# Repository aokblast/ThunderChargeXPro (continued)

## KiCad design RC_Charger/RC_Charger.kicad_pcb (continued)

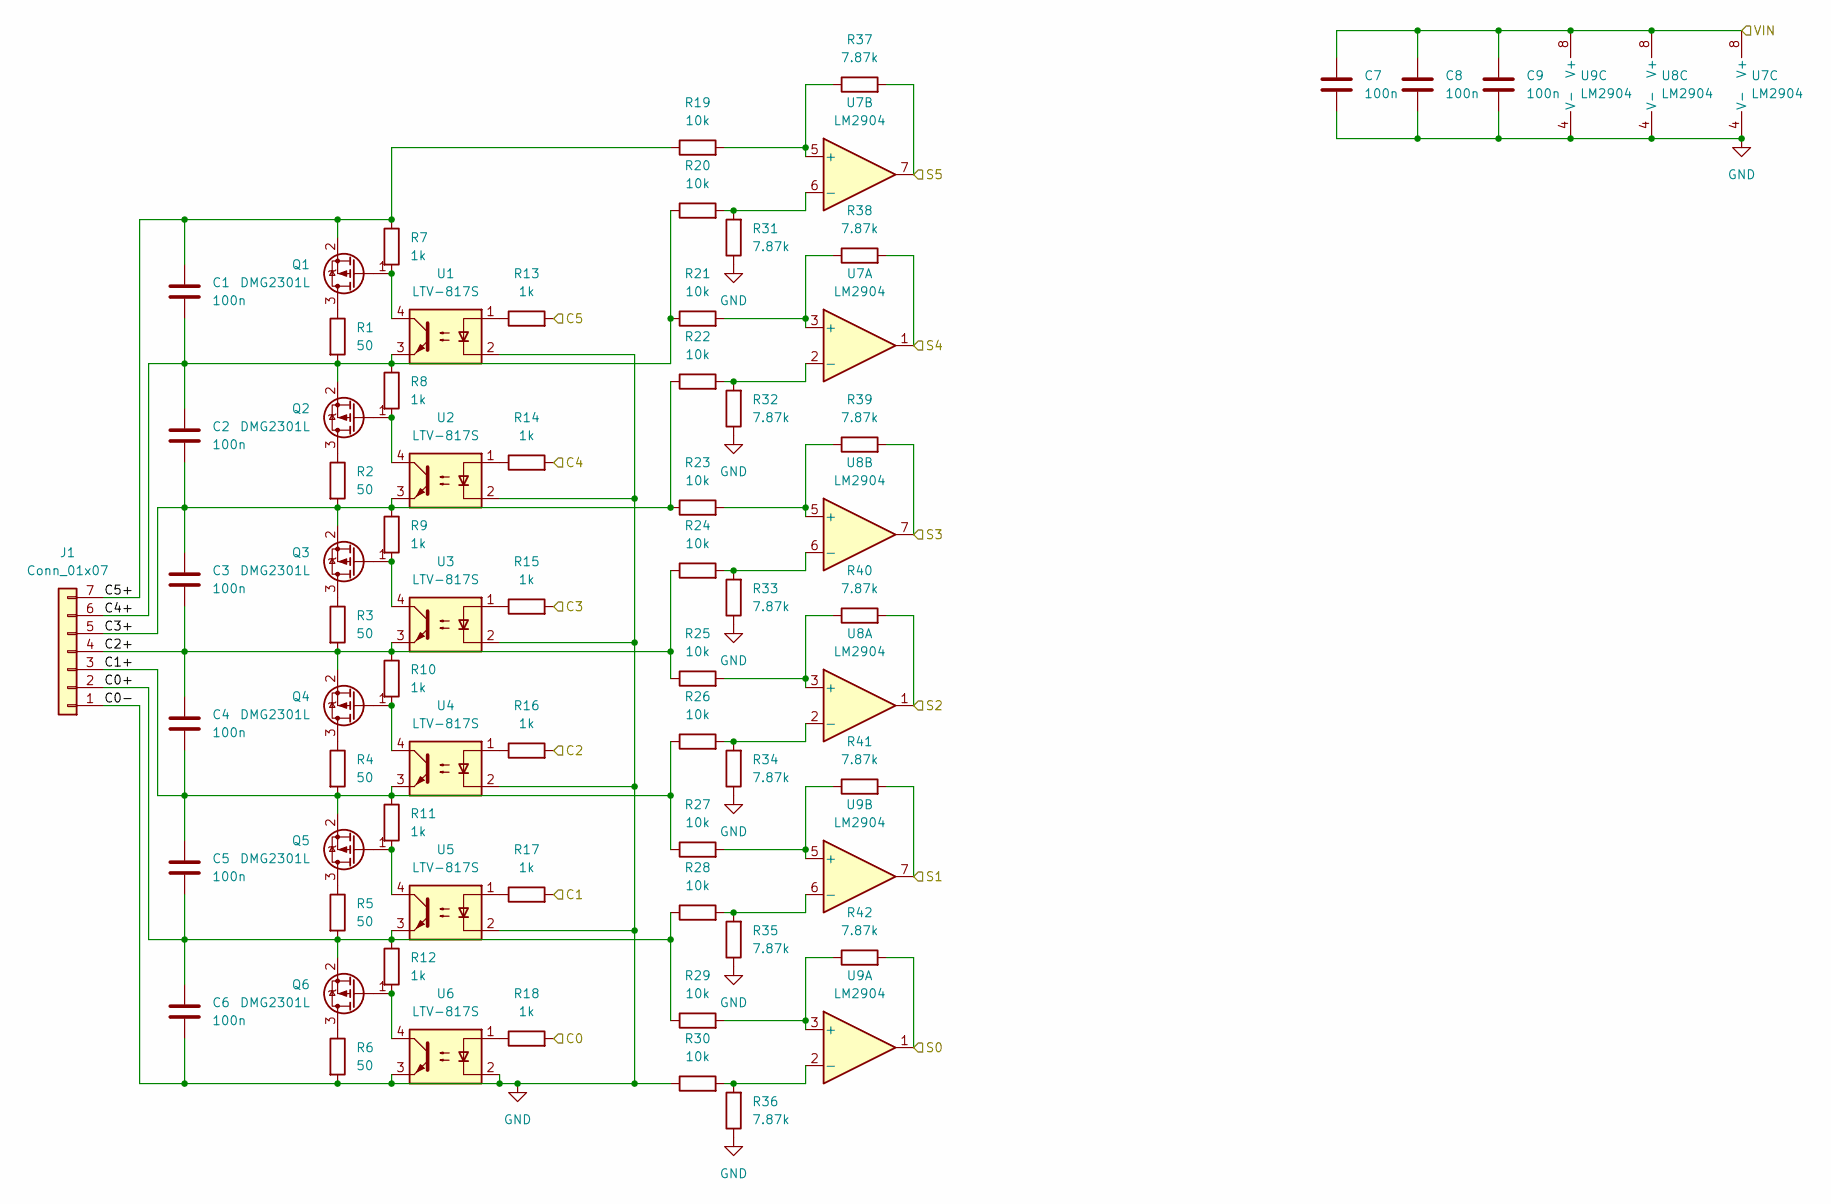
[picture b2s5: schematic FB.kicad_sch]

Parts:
C1, C2, C3, C4, C5, C6, C7, C8, C9: 100n; C_0603_1608Metric
J1: Conn_01x07; JST_XH_B7B-XH-A_1x07_P2.50mm_Vertical
Q1, Q2, Q3, Q4, Q5, Q6: DMG2301L; SOT-23
R1, R2, R3, R4, R5, R6: 50; R_2512_6332Metric
R7, R8, R9, R10, R11, R12, R13, R14, R15, R16, R17, R18: 1k; R_0603_1608Metric
R19, R20, R21, R22, R23, R24, R25, R26, R27, R28, R29, R30: 10k; R_0603_1608Metric
R31, R32, R33, R34, R35, R36, R37, R38, R39, R40, R41, R42: 7.87k; R_0603_1608Metric
U1, U2, U3, U4, U5, U6: LTV-817S; SMDIP-4_W9.53mm
U7, U8, U9: LM2904; SOIC-8_3.9x4.9mm_P1.27mm

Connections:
/BattStage1/Feedback/C0: R18.2; also elsewhere on the board
/BattStage1/Feedback/C0+: C5.2, C6.1, J1.2, Q6.2 (S), R5.2, R12.1, R28.1, R29.1, U5.3
/BattStage1/Feedback/C1: R17.2; also elsewhere on the board
/BattStage1/Feedback/C1+: C4.2, C5.1, J1.3, Q5.2 (S), R4.2, R11.1, R26.1, R27.1, U4.3
/BattStage1/Feedback/C2: R16.2; also elsewhere on the board
/BattStage1/Feedback/C2+: C3.2, C4.1, J1.4, Q4.2 (S), R3.2, R10.1, R24.1, R25.1, U3.3
/BattStage1/Feedback/C3: R15.2; also elsewhere on the board
/BattStage1/Feedback/C3+: C2.2, C3.1, J1.5, Q3.2 (S), R2.2, R9.1, R22.1, R23.1, U2.3
/BattStage1/Feedback/C4: R14.2; also elsewhere on the board
/BattStage1/Feedback/C4+: C1.2, C2.1, J1.6, Q2.2 (S), R1.2, R8.1, R20.1, R21.1, U1.3
/BattStage1/Feedback/C5: R13.2; also elsewhere on the board
/BattStage1/Feedback/C5+: C1.1, J1.7, Q1.2 (S), R7.1, R19.1
/BattStage1/Feedback/S0: R42.2, U9.1; also elsewhere on the board
/BattStage1/Feedback/S1: R41.2, U9.7; also elsewhere on the board
/BattStage1/Feedback/S2: R40.2, U8.1; also elsewhere on the board
/BattStage1/Feedback/S3: R39.2, U8.7; also elsewhere on the board
/BattStage1/Feedback/S4: R38.2, U7.1; also elsewhere on the board
/BattStage1/Feedback/S5: R37.2, U7.7; also elsewhere on the board
GND: C6.2, C7.2, C8.2, C9.2, J1.1, R6.2, R30.1, R31.1, R32.1, R33.1, R34.1, R35.1, R36.1, U1.2, U2.2, U3.2, U4.2, U5.2, U6.2, U6.3, U7.4 (V-), U8.4 (V-), U9.4 (V-); also elsewhere on the board
unnamed: Q1.3 (D), R1.1
unnamed: Q1.1 (G), R7.2, U1.4
unnamed: Q2.3 (D), R2.1
unnamed: Q2.1 (G), R8.2, U2.4
unnamed: Q3.3 (D), R3.1
unnamed: Q3.1 (G), R9.2, U3.4
unnamed: Q4.3 (D), R4.1
unnamed: Q4.1 (G), R10.2, U4.4
unnamed: Q5.3 (D), R5.1
unnamed: Q5.1 (G), R11.2, U5.4
unnamed: Q6.3 (D), R6.1
unnamed: Q6.1 (G), R12.2, U6.4
unnamed: R13.1, U1.1
unnamed: R14.1, U2.1
unnamed: R15.1, U3.1
unnamed: R16.1, U4.1
unnamed: R17.1, U5.1
unnamed: R18.1, U6.1
unnamed: R21.2, R38.1, U7.3 (+)
unnamed: R22.2, R32.2, U7.2 (-)
unnamed: R19.2, R37.1, U7.5 (+)
unnamed: R20.2, R31.2, U7.6 (-)
unnamed: R25.2, R40.1, U8.3 (+)
unnamed: R26.2, R34.2, U8.2 (-)
unnamed: R23.2, R39.1, U8.5 (+)
unnamed: R24.2, R33.2, U8.6 (-)
unnamed: R29.2, R42.1, U9.3 (+)
unnamed: R30.2, R36.2, U9.2 (-)
unnamed: R27.2, R41.1, U9.5 (+)
unnamed: R28.2, R35.2, U9.6 (-)
VCC: C7.1, C8.1, C9.1, U7.8 (V+), U8.8 (V+), U9.8 (V+); also elsewhere on the board

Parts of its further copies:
C82, C83, C84, C85, C86, C87, C88, C89, C90: 100n; C_0603_1608Metric
J6: Conn_01x07; JST_XH_B7B-XH-A_1x07_P2.50mm_Vertical
Q15, Q16, Q17, Q18, Q19, Q20: DMG2301L; SOT-23
R77, R78, R79, R80, R81, R82: 50; R_2512_6332Metric
R83, R84, R85, R86, R87, R88, R89, R90, R91, R92, R93, R94: 1k; R_0603_1608Metric
R95, R96, R97, R98, R99, R100, R101, R102, R103, R104, R105, R106: 10k; R_0603_1608Metric
R107, R108, R109, R110, R111, R112, R113, R114, R115, R116, R117, R118: 7.87k; R_0603_1608Metric
U18, U19, U20, U21, U22, U23: LTV-817S; SMDIP-4_W9.53mm
U24, U25, U26: LM2904; SOIC-8_3.9x4.9mm_P1.27mm

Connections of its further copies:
/BattStage2/Feedback/C0: R94.2; also elsewhere on the board
/BattStage2/Feedback/C0+: C86.2, C87.1, J6.2, Q20.2 (S), R81.2, R88.1, R104.1, R105.1, U22.3
/BattStage2/Feedback/C1: R93.2; also elsewhere on the board
/BattStage2/Feedback/C1+: C85.2, C86.1, J6.3, Q19.2 (S), R80.2, R87.1, R102.1, R103.1, U21.3
/BattStage2/Feedback/C2: R92.2; also elsewhere on the board
/BattStage2/Feedback/C2+: C84.2, C85.1, J6.4, Q18.2 (S), R79.2, R86.1, R100.1, R101.1, U20.3
/BattStage2/Feedback/C3: R91.2; also elsewhere on the board
/BattStage2/Feedback/C3+: C83.2, C84.1, J6.5, Q17.2 (S), R78.2, R85.1, R98.1, R99.1, U19.3
/BattStage2/Feedback/C4: R90.2; also elsewhere on the board
/BattStage2/Feedback/C4+: C82.2, C83.1, J6.6, Q16.2 (S), R77.2, R84.1, R96.1, R97.1, U18.3
/BattStage2/Feedback/C5: R89.2; also elsewhere on the board
/BattStage2/Feedback/C5+: C82.1, J6.7, Q15.2 (S), R83.1, R95.1
/BattStage2/Feedback/S0: R118.2, U26.1; also elsewhere on the board
/BattStage2/Feedback/S1: R117.2, U26.7; also elsewhere on the board
/BattStage2/Feedback/S2: R116.2, U25.1; also elsewhere on the board
/BattStage2/Feedback/S3: R115.2, U25.7; also elsewhere on the board
/BattStage2/Feedback/S4: R114.2, U24.1; also elsewhere on the board
/BattStage2/Feedback/S5: R113.2, U24.7; also elsewhere on the board
GND: C87.2, C88.2, C89.2, C90.2, J6.1, R82.2, R106.1, R107.1, R108.1, R109.1, R110.1, R111.1, R112.1, U18.2, U19.2, U20.2, U21.2, U22.2, U23.2, U23.3, U24.4 (V-), U25.4 (V-), U26.4 (V-); also elsewhere on the board
unnamed: Q15.3 (D), R77.1
unnamed: Q15.1 (G), R83.2, U18.4
unnamed: Q16.3 (D), R78.1
unnamed: Q16.1 (G), R84.2, U19.4
unnamed: Q17.3 (D), R79.1
unnamed: Q17.1 (G), R85.2, U20.4
unnamed: Q18.3 (D), R80.1
unnamed: Q18.1 (G), R86.2, U21.4
unnamed: Q19.3 (D), R81.1
unnamed: Q19.1 (G), R87.2, U22.4
unnamed: Q20.3 (D), R82.1
unnamed: Q20.1 (G), R88.2, U23.4
unnamed: R89.1, U18.1
unnamed: R90.1, U19.1
unnamed: R91.1, U20.1
unnamed: R92.1, U21.1
unnamed: R93.1, U22.1
unnamed: R94.1, U23.1
unnamed: R97.2, R114.1, U24.3 (+)
unnamed: R98.2, R108.2, U24.2 (-)
unnamed: R95.2, R113.1, U24.5 (+)
unnamed: R96.2, R107.2, U24.6 (-)
unnamed: R101.2, R116.1, U25.3 (+)
unnamed: R102.2, R110.2, U25.2 (-)
unnamed: R99.2, R115.1, U25.5 (+)
unnamed: R100.2, R109.2, U25.6 (-)
unnamed: R105.2, R118.1, U26.3 (+)
unnamed: R106.2, R112.2, U26.2 (-)
unnamed: R103.2, R117.1, U26.5 (+)
unnamed: R104.2, R111.2, U26.6 (-)
VCC: C88.1, C89.1, C90.1, U24.8 (V+), U25.8 (V+), U26.8 (V+); also elsewhere on the board

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
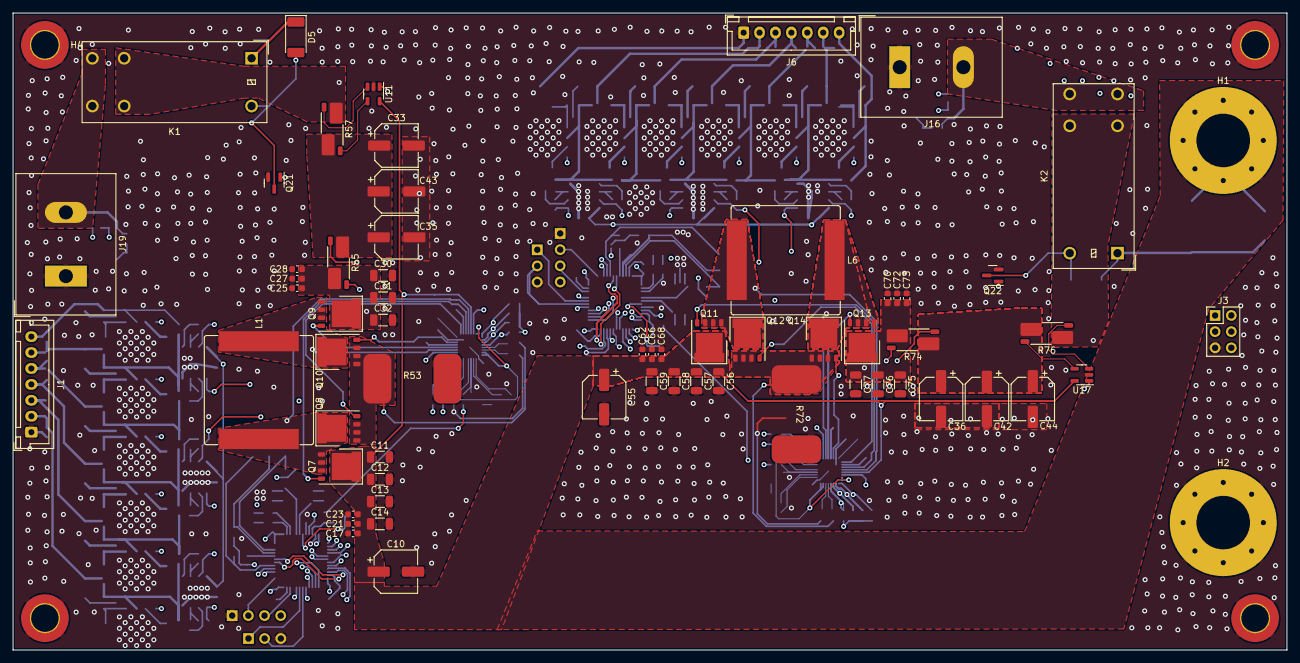
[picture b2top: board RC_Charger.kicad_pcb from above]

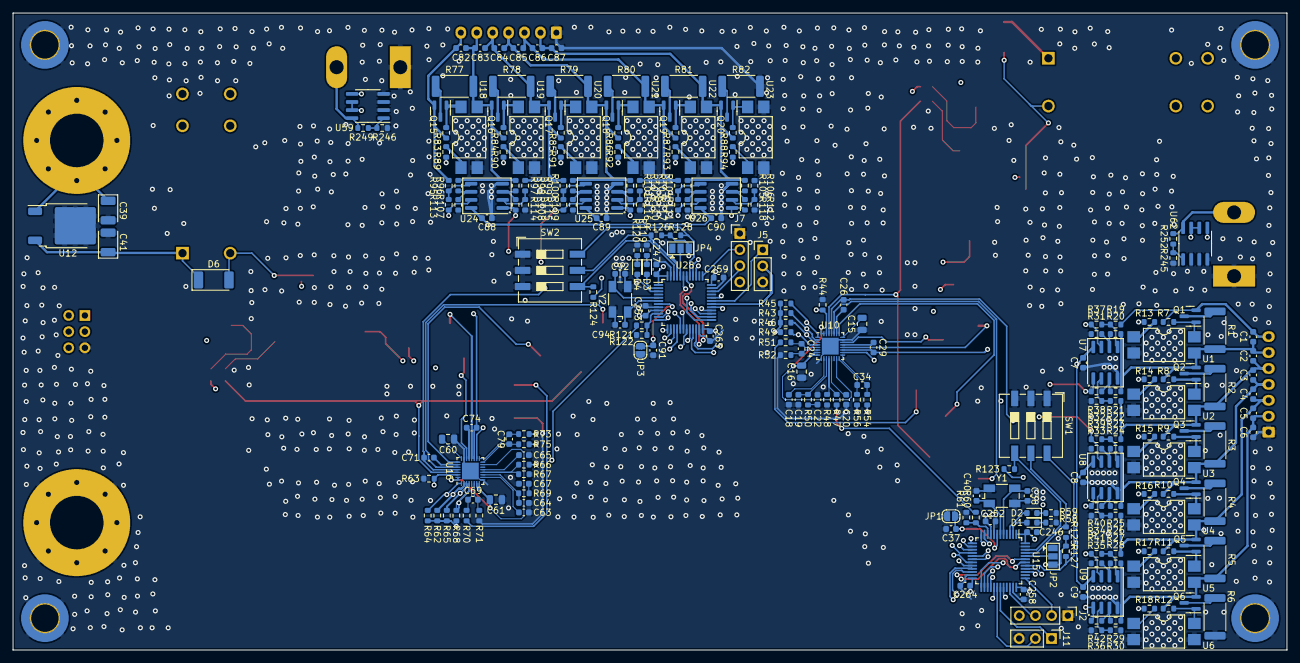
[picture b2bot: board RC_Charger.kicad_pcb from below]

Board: 4 copper layers, 200.0 x 100.0 mm, 302 parts (234 on the bottom side), 211 nets.

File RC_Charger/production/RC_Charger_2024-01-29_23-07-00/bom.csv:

Designator,Footprint,Quantity,Value,LCSC Part #
"C1, C2, C246, C247, C252, C253, C258, C259, C264, C265, C3, C37, C4, C5, C6, C7, C8, C82, C83, C84, C85, C86, C87, C88, C89, C9, C90, C91",0603,28,100n,
"C10, C33, C42, C55",CP_Elec_10x10,4,100u,
"C11, C12, C13, C14, C30, C31, C32, C56, C57, C58, C59, C75, C76, C77",1210,14,10u,
"C15, C16, C60, C61",0805,4,2.2u,
"C17, C21, C23, C25, C27, C28, C62, C66, C68, C70, C72, C73",0603,12,0.1u,
"C18, C63",0603,2,100p,
"C19, C64",0603,2,560p,
"C20, C65",0603,2,47n,
"C22, C67",0603,2,68n,
"C24, C69",0603,2,47p,
"C26, C29, C34, C71, C74, C79",0603,6,0.22u,
"C35, C36, C80, C81",2220,4,22u,
"C38, C40, C92, C94",0603,4,26p 16V,
"C39, C41",CP_EIA-3528-21_Kemet-B,2,10u,
"D1, D2, D3, D4",0603,4,LED,
"D5, D6",D_MELF,2,SM4001,
"H1, H2",MountingHole_8.4mm_M8_Pad_Via,2,M8,
"H3, H4, H5, H6",MountingHole_4.3mm_M4_DIN965_Pad_TopBottom,4,M4,
"J1, J6",JST_XH_B7B-XH-A_1x07_P2.50mm_Vertical,2,Conn_01x07,
"J11, J5",PinHeader_1x03_P2.54mm_Vertical,2,PWR1_DBG,
"J16, J19",TerminalBlock_Dinkle_DT-55-B01X-02_P10.00mm,2,BAT,
"J2, J7",PinHeader_1x04_P2.54mm_Vertical,2,SWD,
J3,PinHeader_2x03_P2.54mm_Vertical,1,Conn_02x03_Odd_Even,
"JP1, JP3",SolderJumper-2_P1.3mm_Open_RoundedPad1.0x1.5mm,2,RST,
"JP2, JP4",SolderJumper-3_P1.3mm_Open_Pad1.0x1.5mm,2,BOOT0,
"K5, K6",T9GV5L145,2,Relay_SPST-NO,
"L1, L6",L_Bourns_SRP1770TA_16.9x16.9mm,2,4.7u,
"Q1, Q15, Q16, Q17, Q18, Q19, Q2, Q20, Q3, Q4, Q5, Q6",SOT-23,12,DMG2301L,
"Q10, Q11, Q12, Q13, Q14, Q7, Q8, Q9",PQFN-8-EP_6x5mm_P1.27mm_Generic,8,IRFH5210,
"Q21, Q22",SOT-23,2,AO3400A,
"R1, R2, R3, R4, R5, R6, R77, R78, R79, R80, R81, R82",2512,12,50,
"R10, R11, R12, R13, R14, R15, R16, R17, R18, R7, R8, R83, R84, R85, R86, R87, R88, R89, R9, R90, R91, R92, R93, R94",0603,24,1k,
"R100, R101, R102, R103, R104, R105, R106, R122, R123, R124, R125, R126, R127, R128, R19, R20, R21, R22, R23, R24, R25, R26, R27, R28, R29, R30, R46, R61, R65, R95, R96, R97, R98, R99",0603,34,10k,
"R107, R108, R109, R110, R111, R112, R113, R114, R115, R116, R117, R118, R31, R32, R33, R34, R35, R36, R37, R38, R39, R40, R41, R42",0603,24,7.87k,
"R119, R120, R58, R59",0603,4,68,
"R121, R60",0603,2,68k,
"R245, R246",0603,2,1.5M,
"R249, R252",0603,2,9.53k,
"R43, R45, R62, R64",0603,4,2.2k,
"R44, R49, R63, R68",0603,4,100k,
"R47, R66",0603,2,42.2k,
"R48, R67",0603,2,3.3k,
"R50, R69",0603,2,2.61k,
"R51, R52, R54, R56, R70, R71, R73, R75",0603,8,100,
"R53, R57, R72, R76",WSLP27265L000FEA,4,4m,
"R55, R74",WSLP27265L000FEA,2,3m,
"SW1, SW2",SW_DIP_SPSTx03_Slide_9.78x9.8mm_W8.61mm_P2.54mm,2,SW_DIP_x03,
"U1, U18, U19, U2, U20, U21, U22, U23, U3, U4, U5, U6",SMDIP-4_W9.53mm,12,LTV-817S,
"U10, U16",QFN-32-1EP_4x4mm_P0.4mm_EP2.65x2.65mm,2,MP2984,
"U11, U17",SOT-23-5,2,INA180A1,
U12,TO-252-2,1,L7805,
"U15, U28",LQFP-48_7x7mm_P0.5mm,2,STM32F103C8Tx,
"U24, U25, U26, U7, U8, U9",SOIC-8_3.9x4.9mm_P1.27mm,6,LM2904,
"U59, U62",SOIC-8_3.9x4.9mm_P1.27mm,2,INA240A1D,
"Y1, Y2",Crystal_SMD_Abracon_ABM3B-4Pin_5.0x3.2mm,2,8M,

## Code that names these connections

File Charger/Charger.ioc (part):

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Mcu.Name=STM32H745ZITx
Mcu.Package=LQFP144
Mcu.UserName=STM32H745ZITx
PA1.GPIOParameters=GPIO_Speed,PinAttribute
PA1.GPIO_Speed=GPIO_SPEED_FREQ_VERY_HIGH
PA1.Mode=RMII
PA1.PinAttribute=CortexM7
PA1.Signal=ETH_REF_CLK
PA11.GPIOParameters=PinAttribute
PA11.Mode=Device_Only
PA11.PinAttribute=CortexM7
PA11.Signal=USB_OTG_FS_DM
PA12.GPIOParameters=PinAttribute
PA12.Mode=Device_Only
PA12.PinAttribute=CortexM7
PA12.Signal=USB_OTG_FS_DP
PA2.GPIOParameters=GPIO_Speed,PinAttribute
PA2.GPIO_Speed=GPIO_SPEED_FREQ_VERY_HIGH
PA2.Mode=RMII
PA2.PinAttribute=CortexM7
PA2.Signal=ETH_MDIO
PA4.GPIOParameters=PinAttribute
PA4.Mode=Half_Duplex_Master_Tx
PA4.PinAttribute=CortexM7
PA4.Signal=I2S1_WS
PA5.GPIOParameters=GPIO_Label,PinAttribute
PA5.GPIO_Label=FAN_CTRL
PA5.PinAttribute=Free
PA5.Signal=GPIO_Output
PA7.GPIOParameters=GPIO_Speed,PinAttribute
PA7.GPIO_Speed=GPIO_SPEED_FREQ_VERY_HIGH
PA7.Mode=RMII
PA7.PinAttribute=CortexM7
PA7.Signal=ETH_CRS_DV
PA8.GPIOParameters=PinAttribute
PA8.Mode=Activate_SOF_FS
PA8.PinAttribute=CortexM7
PA8.Signal=USB_OTG_FS_SOF
PA9.GPIOParameters=PinAttribute
PA9.Mode=Activate_VBUS
PA9.PinAttribute=CortexM7
PA9.Signal=USB_OTG_FS_VBUS
PB0.ContextOwner=CortexM7
PB0.GPIOParameters=GPIO_Label,PinAttribute
PB0.GPIO_Label=LD1 [Green Led]
PB0.PinAttribute=CortexM7
PB0.Signal=GPIO_Output
PB10.GPIOParameters=PinAttribute
PB10.Mode=I2C
PB10.PinAttribute=CortexM4
PB10.Signal=I2C2_SCL
PB11.GPIOParameters=PinAttribute
PB11.Mode=I2C
PB11.PinAttribute=CortexM4
PB11.Signal=I2C2_SDA
PB12.GPIOParameters=GPIO_Label,PinAttribute
PB12.GPIO_Label=T_IRQ
PB12.PinAttribute=Free
PB12.Signal=GPXTI12
PB13.GPIOParameters=GPIO_Speed,PinAttribute
PB13.GPIO_Speed=GPIO_SPEED_FREQ_VERY_HIGH
PB13.Mode=RMII
PB13.PinAttribute=CortexM7
PB13.Signal=ETH_TXD1
PB14.ContextOwner=CortexM7
PB14.GPIOParameters=GPIO_Label,PinAttribute
PB14.GPIO_Label=LD3 [Red Led]
PB14.PinAttribute=CortexM7
PB14.Signal=GPIO_Output
PB15.GPIOParameters=PinAttribute
PB15.Mode=Asynchronous
PB15.PinAttribute=CortexM4
PB15.Signal=USART1_RX
PB2.GPIOParameters=PinAttribute
PB2.Mode=Full_Duplex_Master
PB2.PinAttribute=CortexM7
PB2.Signal=SPI3_MOSI
PB3\ (JTDO/TRACESWO).GPIOParameters=PinAttribute
PB3\ (JTDO/TRACESWO).Mode=Half_Duplex_Master_Tx
PB3\ (JTDO/TRACESWO).PinAttribute=CortexM7
PB3\ (JTDO/TRACESWO).Signal=I2S1_CK
PB6.GPIOParameters=PinAttribute
PB6.Mode=Asynchronous
PB6.PinAttribute=CortexM4
PB6.Signal=USART1_TX
PB7.GPIOParameters=PinAttribute
PB7.Mode=I2C
PB7.PinAttribute=CortexM4
PB7.Signal=I2C1_SDA
PB8.GPIOParameters=PinAttribute
PB8.Mode=I2C
PB8.PinAttribute=CortexM4
PB8.Signal=I2C1_SCL
PC0.GPIOParameters=GPIO_Label,PinAttribute
PC0.GPIO_Label=esnesV
PC0.PinAttribute=CortexM4
PC0.Signal=ADCx_INP10
PC1.GPIOParameters=GPIO_Speed,PinAttribute
PC1.GPIO_Speed=GPIO_SPEED_FREQ_VERY_HIGH
PC1.Mode=RMII
PC1.PinAttribute=CortexM7
PC1.Signal=ETH_MDC
PC10.GPIOParameters=PinAttribute
PC10.Mode=Full_Duplex_Master
PC10.PinAttribute=CortexM7
PC10.Signal=SPI3_SCK
PC11.GPIOParameters=PinAttribute
PC11.Mode=Full_Duplex_Master
PC11.PinAttribute=CortexM7
PC11.Signal=SPI3_MISO
PC12.GPIOParameters=PinAttribute
PC12.Mode=SD_1_bit
PC12.PinAttribute=CortexM7
PC12.Signal=SDMMC1_CK
PC13.GPIOParameters=GPIO_Label,PinAttribute
PC13.GPIO_Label=B1 [Blue PushButton]
PC13.PinAttribute=Free
PC13.Signal=GPIO_Input
PC14-OSC32_IN\ (OSC32_IN).GPIOParameters=PinAttribute
PC14-OSC32_IN\ (OSC32_IN).Mode=LSE-External-Oscillator
PC14-OSC32_IN\ (OSC32_IN).PinAttribute=CortexM7
PC14-OSC32_IN\ (OSC32_IN).Signal=RCC_OSC32_IN
PC15-OSC32_OUT\ (OSC32_OUT).GPIOParameters=PinAttribute
PC15-OSC32_OUT\ (OSC32_OUT).Mode=LSE-External-Oscillator
PC15-OSC32_OUT\ (OSC32_OUT).PinAttribute=CortexM7
PC15-OSC32_OUT\ (OSC32_OUT).Signal=RCC_OSC32_OUT
PC2_C.GPIOParameters=PinAttribute
PC2_C.Mode=Full_Duplex_Master
PC2_C.PinAttribute=CortexM7
PC2_C.Signal=SPI2_MISO
PC3_C.GPIOParameters=PinAttribute
PC3_C.Mode=Full_Duplex_Master
PC3_C.PinAttribute=CortexM7
PC3_C.Signal=SPI2_MOSI
PC4.GPIOParameters=GPIO_Speed,PinAttribute
PC4.GPIO_Speed=GPIO_SPEED_FREQ_VERY_HIGH
PC4.Mode=RMII
PC4.PinAttribute=CortexM7
PC4.Signal=ETH_RXD0
PC5.GPIOParameters=GPIO_Speed,PinAttribute
PC5.GPIO_Speed=GPIO_SPEED_FREQ_VERY_HIGH
PC5.Mode=RMII
PC5.PinAttribute=CortexM7
PC5.Signal=ETH_RXD1
PC8.GPIOParameters=PinAttribute
PC8.Mode=SD_1_bit
PC8.PinAttribute=CortexM7
PC8.Signal=SDMMC1_D0
PD10.GPIOParameters=GPIO_Label,PinAttribute
PD10.GPIO_Label=USB_OTG_FS_PWR_EN
PD10.PinAttribute=Free
PD10.Signal=GPIO_Output
PD2.GPIOParameters=PinAttribute
PD2.Mode=SD_1_bit
PD2.PinAttribute=CortexM7
PD2.Signal=SDMMC1_CMD
PD3.GPIOParameters=PinAttribute
PD3.Mode=Full_Duplex_Master
PD3.PinAttribute=CortexM7
PD3.Signal=SPI2_SCK
PD7.GPIOParameters=PinAttribute
PD7.Mode=Half_Duplex_Master_Tx
PD7.PinAttribute=CortexM7
PD7.Signal=I2S1_SDO
PD8.GPIOParameters=GPIO_Label,PinAttribute
PD8.GPIO_Label=STLINK_RX
PD8.PinAttribute=CortexM4
PD8.Signal=USART3_TX
PD9.GPIOParameters=GPIO_Label,PinAttribute
PD9.GPIO_Label=STLINK_TX
PD9.PinAttribute=CortexM4
PD9.Signal=USART3_RX
PE1.ContextOwner=CortexM7
PE1.GPIOParameters=GPIO_Label,PinAttribute
PE1.GPIO_Label=LD2 [Yellow Led]
PE1.PinAttribute=CortexM7
PE1.Signal=GPIO_Output
PE10.GPIOParameters=GPIO_Label,PinAttribute
PE10.GPIO_Label=Mute
PE10.PinAttribute=Free
PE10.Signal=GPIO_Output
PE11.GPIOParameters=GPIO_Label,PinAttribute
PE11.GPIO_Label=SERVO2
PE11.PinAttribute=CortexM4
PE11.Signal=S_TIM1_CH2
PE12.GPIOParameters=GPIO_Label,PinAttribute
PE12.GPIO_Label=S_CS
PE12.PinAttribute=Free
PE12.Signal=GPIO_Output
PE13.GPIOParameters=GPIO_Label,PinAttribute
PE13.GPIO_Label=S_RST
PE13.PinAttribute=Free
PE13.Signal=GPIO_Output
PE14.GPIOParameters=GPIO_Label,PinAttribute
PE14.GPIO_Label=S_DCRS
PE14.PinAttribute=Free
PE14.Signal=GPIO_Output
PE7.GPIOParameters=GPIO_Label,PinAttribute
PE7.GPIO_Label=T_CS
PE7.PinAttribute=Free
PE7.Signal=GPIO_Output
PE9.GPIOParameters=GPIO_Label,PinAttribute
PE9.GPIO_Label=SERVO1
PE9.PinAttribute=CortexM4
PE9.Signal=S_TIM1_CH1
PF11.GPIOParameters=GPIO_Label,PinAttribute
PF11.GPIO_Label=esnesI
PF11.Mode=IN2-Single-Ended
PF11.PinAttribute=CortexM4
PF11.Signal=ADC1_INP2
PG11.GPIOParameters=GPIO_Speed,PinAttribute
PG11.GPIO_Speed=GPIO_SPEED_FREQ_VERY_HIGH
PG11.Mode=RMII
PG11.PinAttribute=CortexM7
PG11.Signal=ETH_TX_EN
PG13.GPIOParameters=GPIO_Speed,PinAttribute
PG13.GPIO_Speed=GPIO_SPEED_FREQ_VERY_HIGH
PG13.Mode=RMII
PG13.PinAttribute=CortexM7
PG13.Signal=ETH_TXD0
PG7.GPIOParameters=GPIO_Label,PinAttribute
PG7.GPIO_Label=USB_OTG_FS_OVCR
PG7.PinAttribute=Free
PG7.Signal=GPXTI7
PH0-OSC_IN\ (PH0).GPIOParameters=PinAttribute
PH0-OSC_IN\ (PH0).Mode=HSE-External-Clock-Source
PH0-OSC_IN\ (PH0).PinAttribute=CortexM7
PH0-OSC_IN\ (PH0).Signal=RCC_OSC_IN
PH1-OSC_OUT\ (PH1).GPIOParameters=PinAttribute
PH1-OSC_OUT\ (PH1).PinAttribute=CortexM7
PH1-OSC_OUT\ (PH1).Signal=RCC_OSC_OUT
RCC.HSE_VALUE=8000000
RCC.SYSCLKFreq_VALUE=400000000
RCC.SYSCLKSource=RCC_SYSCLKSOURCE_PLLCLK
board=NUCLEO-H745ZI-Q
boardIOC=true

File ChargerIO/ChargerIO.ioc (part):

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Mcu.Name=STM32F103C(8-B)Tx
Mcu.Package=LQFP48
Mcu.UserName=STM32F103C8Tx
PA0-WKUP.GPIOParameters=GPIO_Label
PA0-WKUP.GPIO_Label=VOUT
PA0-WKUP.Signal=ADCx_IN0
PA1.GPIOParameters=GPIO_Label
PA1.GPIO_Label=IOUT
PA1.Signal=ADCx_IN1
PA10.Mode=Asynchronous
PA10.Signal=USART1_RX
PA11.GPIOParameters=GPIO_Label
PA11.GPIO_Label=OUT_EN
PA11.Signal=GPIO_Output
PA13.Mode=Serial_Wire
PA13.Signal=SYS_JTMS-SWDIO
PA14.Mode=Serial_Wire
PA14.Signal=SYS_JTCK-SWCLK
PA2.GPIOParameters=GPIO_Label
PA2.GPIO_Label=VB0
PA2.Signal=ADCx_IN2
PA3.GPIOParameters=GPIO_Label
PA3.GPIO_Label=VB1
PA3.Signal=ADCx_IN3
PA4.GPIOParameters=GPIO_Label
PA4.GPIO_Label=VB2
PA4.Signal=ADCx_IN4
PA5.GPIOParameters=GPIO_Label
PA5.GPIO_Label=VB3
PA5.Signal=ADCx_IN5
PA6.GPIOParameters=GPIO_Label
PA6.GPIO_Label=VB4
PA6.Signal=ADCx_IN6
PA7.GPIOParameters=GPIO_Label
PA7.GPIO_Label=VB5
PA7.Signal=ADCx_IN7
PA8.Signal=S_TIM1_CH1
PA9.Mode=Asynchronous
PA9.Signal=USART1_TX
PB0.GPIOParameters=GPIO_Label
PB0.GPIO_Label=VBATTOUT
PB0.Signal=ADCx_IN8
PB1.GPIOParameters=GPIO_Label
PB1.GPIO_Label=PWM_ERR
PB1.Signal=GPXTI1
PB10.Mode=I2C
PB10.Signal=I2C2_SCL
PB11.Mode=I2C
PB11.Signal=I2C2_SDA
PB12.GPIOParameters=GPIO_Label
PB12.GPIO_Label=BAL_C2
PB12.Signal=GPIO_Output
PB13.GPIOParameters=GPIO_Label
PB13.GPIO_Label=BAL_C3
PB13.Signal=GPIO_Output
PB14.GPIOParameters=GPIO_Label
PB14.GPIO_Label=BAL_C4
PB14.Signal=GPIO_Output
PB15.GPIOParameters=GPIO_Label
PB15.GPIO_Label=BAL_C5
PB15.Signal=GPIO_Output
PB2.GPIOParameters=GPIO_Label
PB2.GPIO_Label=PWM_EN
PB2.Signal=GPIO_Output
PB3.GPIOParameters=GPIO_Label
PB3.GPIO_Label=BAL_C0
PB3.Signal=GPIO_Output
PB4.GPIOParameters=GPIO_Label
PB4.GPIO_Label=BAL_C1
PB4.Signal=GPIO_Output
PB5.GPIOParameters=GPIO_Label
PB5.GPIO_Label=ADDR2
PB5.Signal=GPIO_Input
PB6.Mode=I2C
PB6.Signal=I2C1_SCL
PB7.Mode=I2C
PB7.Signal=I2C1_SDA
PB8.GPIOParameters=GPIO_Label
PB8.GPIO_Label=ADDR1
PB8.Signal=GPIO_Input
PB9.GPIOParameters=GPIO_Label
PB9.GPIO_Label=ADDR0
PB9.Signal=GPIO_Input
PC13-TAMPER-RTC.GPIOParameters=GPIO_Label
PC13-TAMPER-RTC.GPIO_Label=LED1
PC13-TAMPER-RTC.Signal=GPIO_Output
PC14-OSC32_IN.GPIOParameters=GPIO_Label
PC14-OSC32_IN.GPIO_Label=LED2
PC14-OSC32_IN.Signal=GPIO_Output
PD0-OSC_IN.Mode=HSE-External-Clock-Source
PD0-OSC_IN.Signal=RCC_OSC_IN
PD1-OSC_OUT.Mode=HSE-External-Clock-Source
PD1-OSC_OUT.Signal=RCC_OSC_OUT
board=custom

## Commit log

2024-01-20 init pin define
2024-01-20 Change UART pin
2024-01-20 fix PA4 PB5 conflict
2024-01-20 Add Mute Pin
2024-01-20 change 4*uart to i2c
2024-01-21 feat: Add RTOS and lwip
2024-01-24 Add reverse voltage protection control
2024-01-24 add screen pins
2024-01-26 change Screen Pins
2024-01-27 change Vsense Pin
2024-01-28 Add Address Pins
2024-01-28 Add Board Files
2024-01-29 Change MainBoard Serov Position
2024-01-29 Change Charger Power Board Clearance Settings
2024-02-06 Change components for costdown
2024-02-09 Add full bom and final pcb design
2024-02-23 Add html bom
